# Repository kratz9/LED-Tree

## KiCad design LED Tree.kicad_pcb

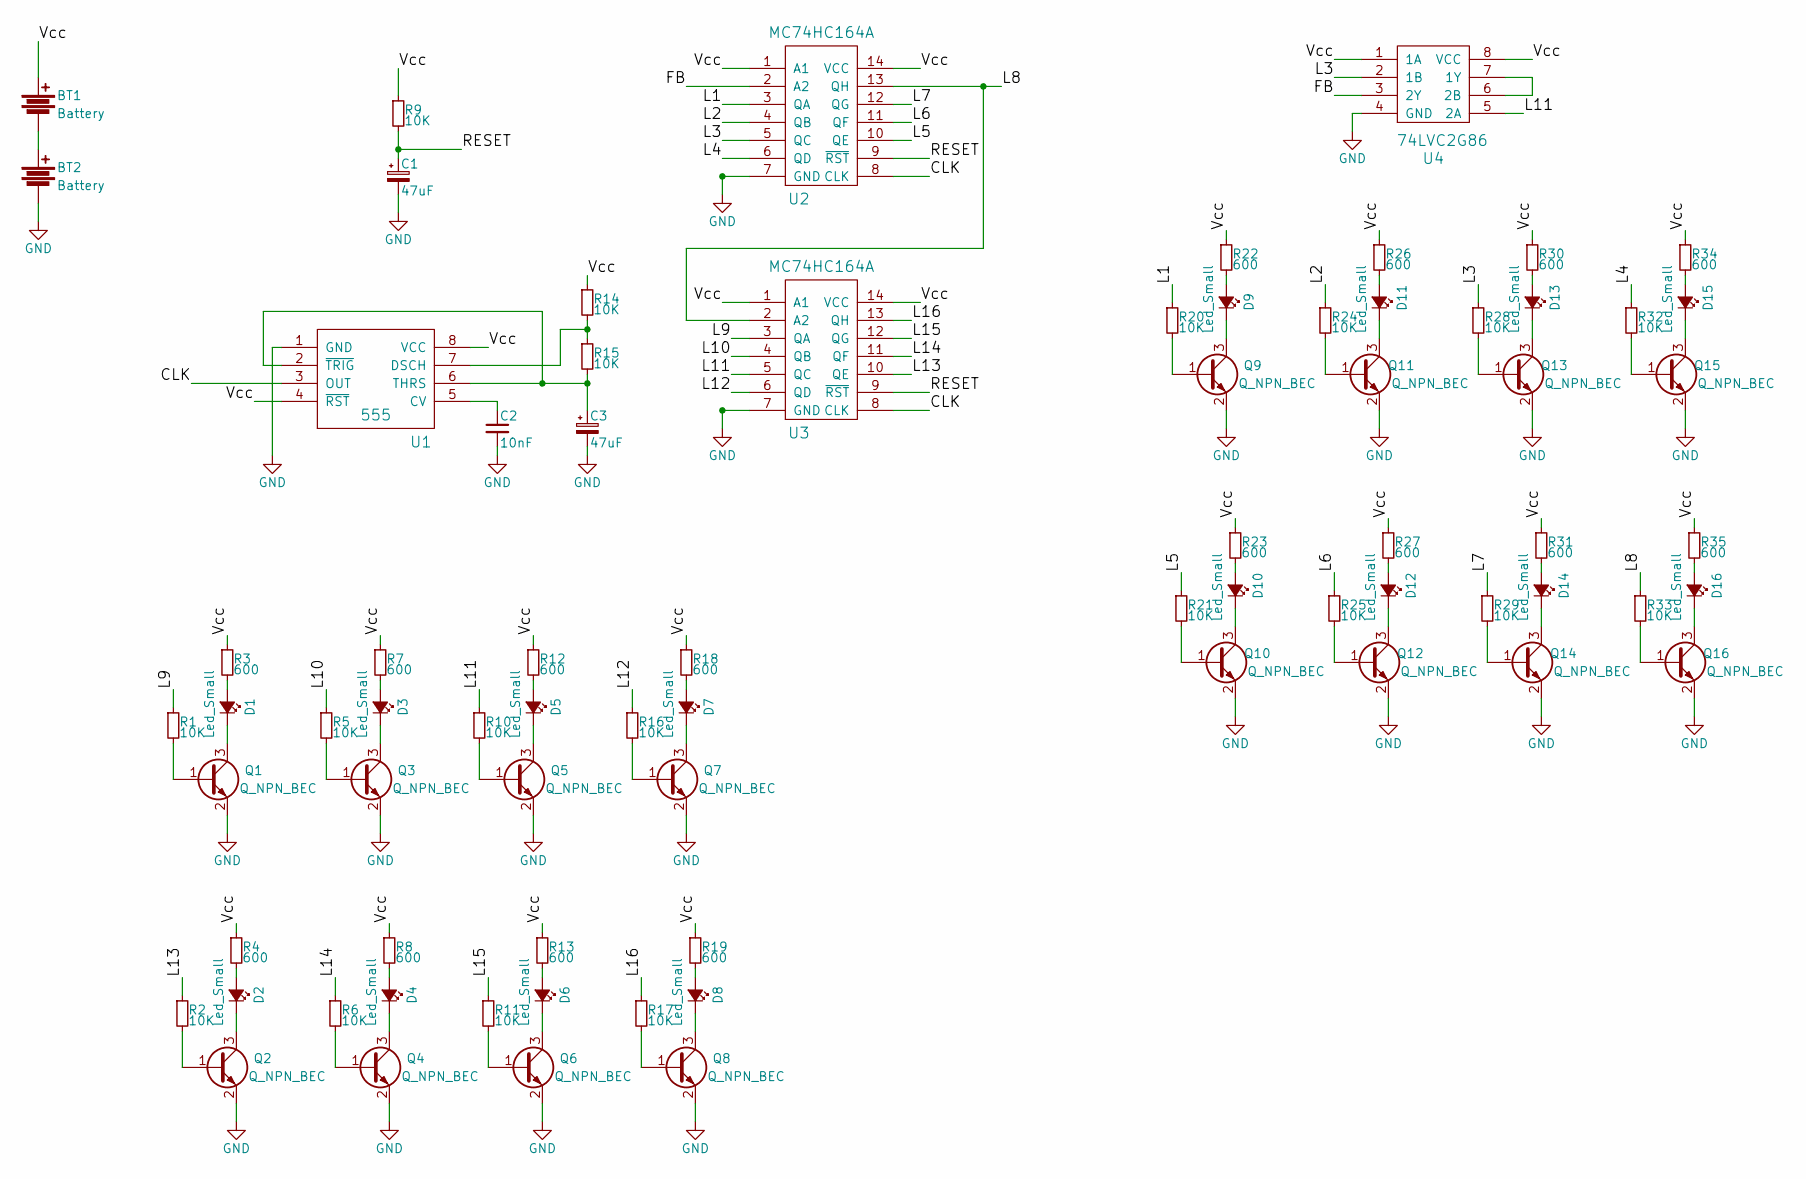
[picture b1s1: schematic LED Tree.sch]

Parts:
BT1, BT2: Battery
C1, C3: 47uF; c_elec_4x4.5
C2: 10nF; C_0805_HandSoldering
D1, D2, D3, D4, D5, D6, D7, D8, D9, D10, D11, D12, D13, D14, D15, D16: Led_Small; LED_0805
Q1, Q2, Q3, Q4, Q5, Q6, Q7, Q8, Q9, Q10, Q11, Q12, Q13, Q14, Q15, Q16: Q_NPN_BEC; SOT-23
R1, R2, R5, R6, R9, R10, R11, R14, R15, R16, R17, R20, R21, R24, R25, R28, R29, R32, R33: 10K; R_0805_HandSoldering
R3, R4, R7, R8, R12, R13, R18, R19, R22, R23, R26, R27, R30, R31, R34, R35: 600; R_0805_HandSoldering
U1: 555; SOIC-8-N
U2, U3: MC74HC164A; SSOP-14
U4: 74LVC2G86; TSSOP-8_3x3mm_Pitch0.65mm

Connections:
/CLK: U1.3 (OUT), U2.8 (CLK), U3.8 (CLK)
/FB: U2.2 (A2), U4.3 (2Y)
/L1: R20.1, U2.3 (QA)
/L2: R24.1, U2.4 (QB)
/L3: R28.1, U2.5 (QC), U4.2 (1B)
/L4: R32.1, U2.6 (QD)
/L5: R21.1, U2.10 (QE)
/L6: R25.1, U2.11 (QF)
/L7: R29.1, U2.12 (QG)
/L8: R33.1, U2.13 (QH), U3.2 (A2)
/L9: R1.1, U3.3 (QA)
/L10: R5.1, U3.4 (QB)
/L11: R10.1, U3.5 (QC), U4.5 (2A)
/L12: R16.1, U3.6 (QD)
/L13: R2.1, U3.10 (QE)
/L14: R6.1, U3.11 (QF)
/L15: R11.1, U3.12 (QG)
/L16: R17.1, U3.13 (QH)
/RESET: C1.1, R9.2, U2.9 (~RST), U3.9 (~RST)
/Vcc: BT1.1, R3.1, R4.1, R7.1, R8.1, R9.1, R12.1, R13.1, R14.1, R18.1, R19.1, R22.1, R23.1, R26.1, R27.1, R30.1, R31.1, R34.1, R35.1, U1.4 (~RST), U1.8 (VCC), U2.1 (A1), U2.14 (VCC), U3.1 (A1), U3.14 (VCC), U4.1 (1A), U4.8 (VCC)
GND: BT2.2, C1.2, C2.2, C3.2, Q1.2 (E), Q2.2 (E), Q3.2 (E), Q4.2 (E), Q5.2 (E), Q6.2 (E), Q7.2 (E), Q8.2 (E), Q9.2 (E), Q10.2 (E), Q11.2 (E), Q12.2 (E), Q13.2 (E), Q14.2 (E), Q15.2 (E), Q16.2 (E), U1.1 (GND), U2.7 (GND), U3.7 (GND), U4.4 (GND)
unnamed: BT1.2, BT2.1
unnamed: C2.1, U1.5 (CV)
unnamed: C3.1, R15.2, U1.2 (~TRIG), U1.6 (THRS)
unnamed: D1.1 (K), Q1.3 (C)
unnamed: D1.2 (A), R3.2
unnamed: D2.1 (K), Q2.3 (C)
unnamed: D2.2 (A), R4.2
unnamed: D3.1 (K), Q3.3 (C)
unnamed: D3.2 (A), R7.2
unnamed: D4.1 (K), Q4.3 (C)
unnamed: D4.2 (A), R8.2
unnamed: D5.1 (K), Q5.3 (C)
unnamed: D5.2 (A), R12.2
unnamed: D6.1 (K), Q6.3 (C)
unnamed: D6.2 (A), R13.2
unnamed: D7.1 (K), Q7.3 (C)
unnamed: D7.2 (A), R18.2
unnamed: D8.1 (K), Q8.3 (C)
unnamed: D8.2 (A), R19.2
unnamed: D9.1 (K), Q9.3 (C)
unnamed: D9.2 (A), R22.2
unnamed: D10.1 (K), Q10.3 (C)
unnamed: D10.2 (A), R23.2
unnamed: D11.1 (K), Q11.3 (C)
unnamed: D11.2 (A), R26.2
unnamed: D12.1 (K), Q12.3 (C)
unnamed: D12.2 (A), R27.2
unnamed: D13.1 (K), Q13.3 (C)
unnamed: D13.2 (A), R30.2
unnamed: D14.1 (K), Q14.3 (C)
unnamed: D14.2 (A), R31.2
unnamed: D15.1 (K), Q15.3 (C)
unnamed: D15.2 (A), R34.2
unnamed: D16.1 (K), Q16.3 (C)
unnamed: D16.2 (A), R35.2
unnamed: Q1.1 (B), R1.2
unnamed: Q2.1 (B), R2.2
unnamed: Q3.1 (B), R5.2
unnamed: Q4.1 (B), R6.2
unnamed: Q5.1 (B), R10.2
unnamed: Q6.1 (B), R11.2
unnamed: Q7.1 (B), R16.2
unnamed: Q8.1 (B), R17.2
unnamed: Q9.1 (B), R20.2
unnamed: Q10.1 (B), R21.2
unnamed: Q11.1 (B), R24.2
unnamed: Q12.1 (B), R25.2
unnamed: Q13.1 (B), R28.2
unnamed: Q14.1 (B), R29.2
unnamed: Q15.1 (B), R32.2
unnamed: Q16.1 (B), R33.2
unnamed: R14.2, R15.1, U1.7 (DSCH)
unnamed: U4.6 (2B), U4.7 (1Y)

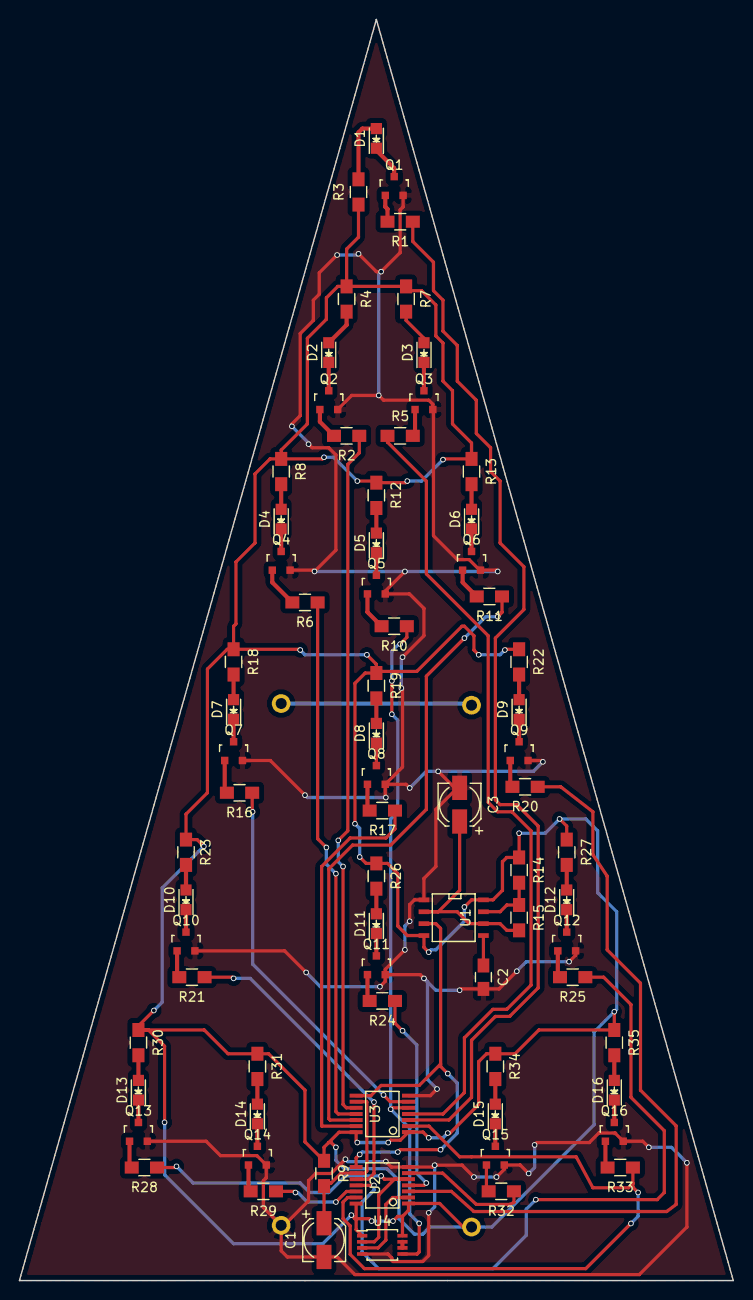
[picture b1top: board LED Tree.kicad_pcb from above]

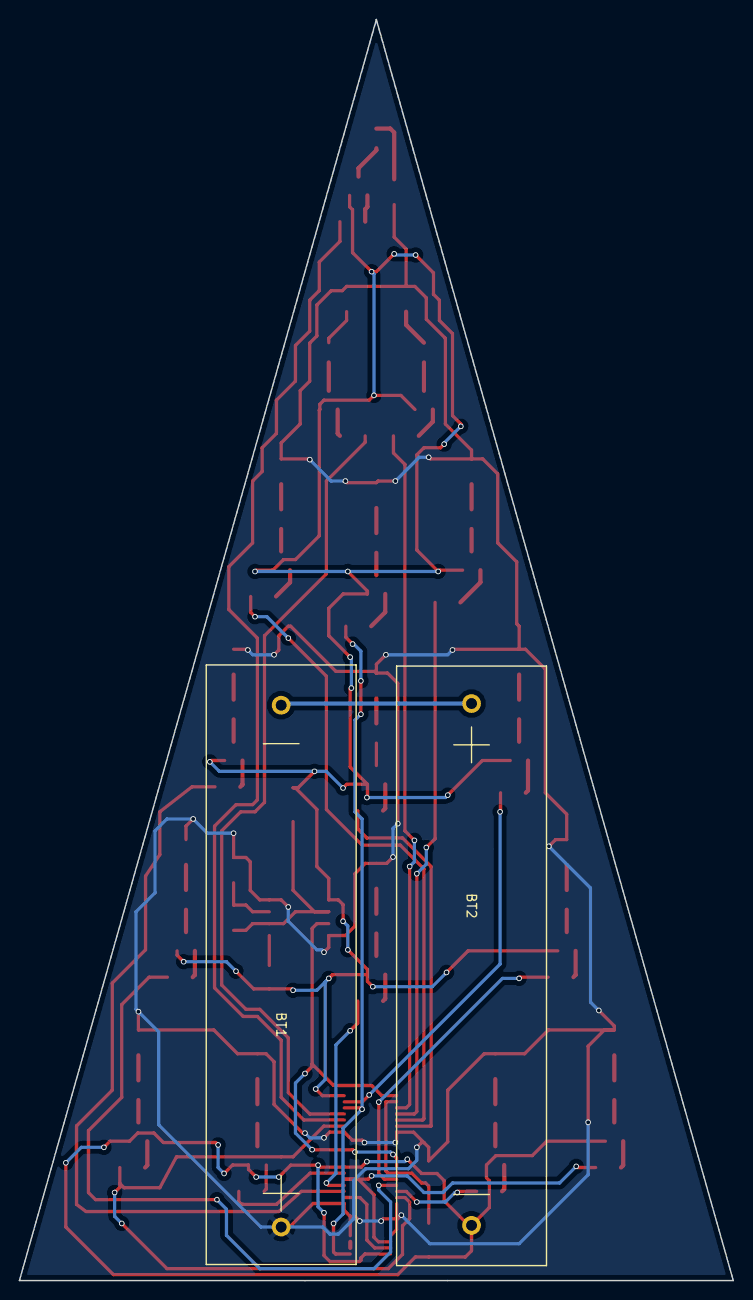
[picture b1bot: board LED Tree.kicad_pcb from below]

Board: 2 copper layers, 76.2 x 134.6 mm, 76 parts (2 on the bottom side), 74 nets.

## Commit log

2016-12-09 :space_invader: Added .gitattributes & .gitignore files
2016-12-16 initial
